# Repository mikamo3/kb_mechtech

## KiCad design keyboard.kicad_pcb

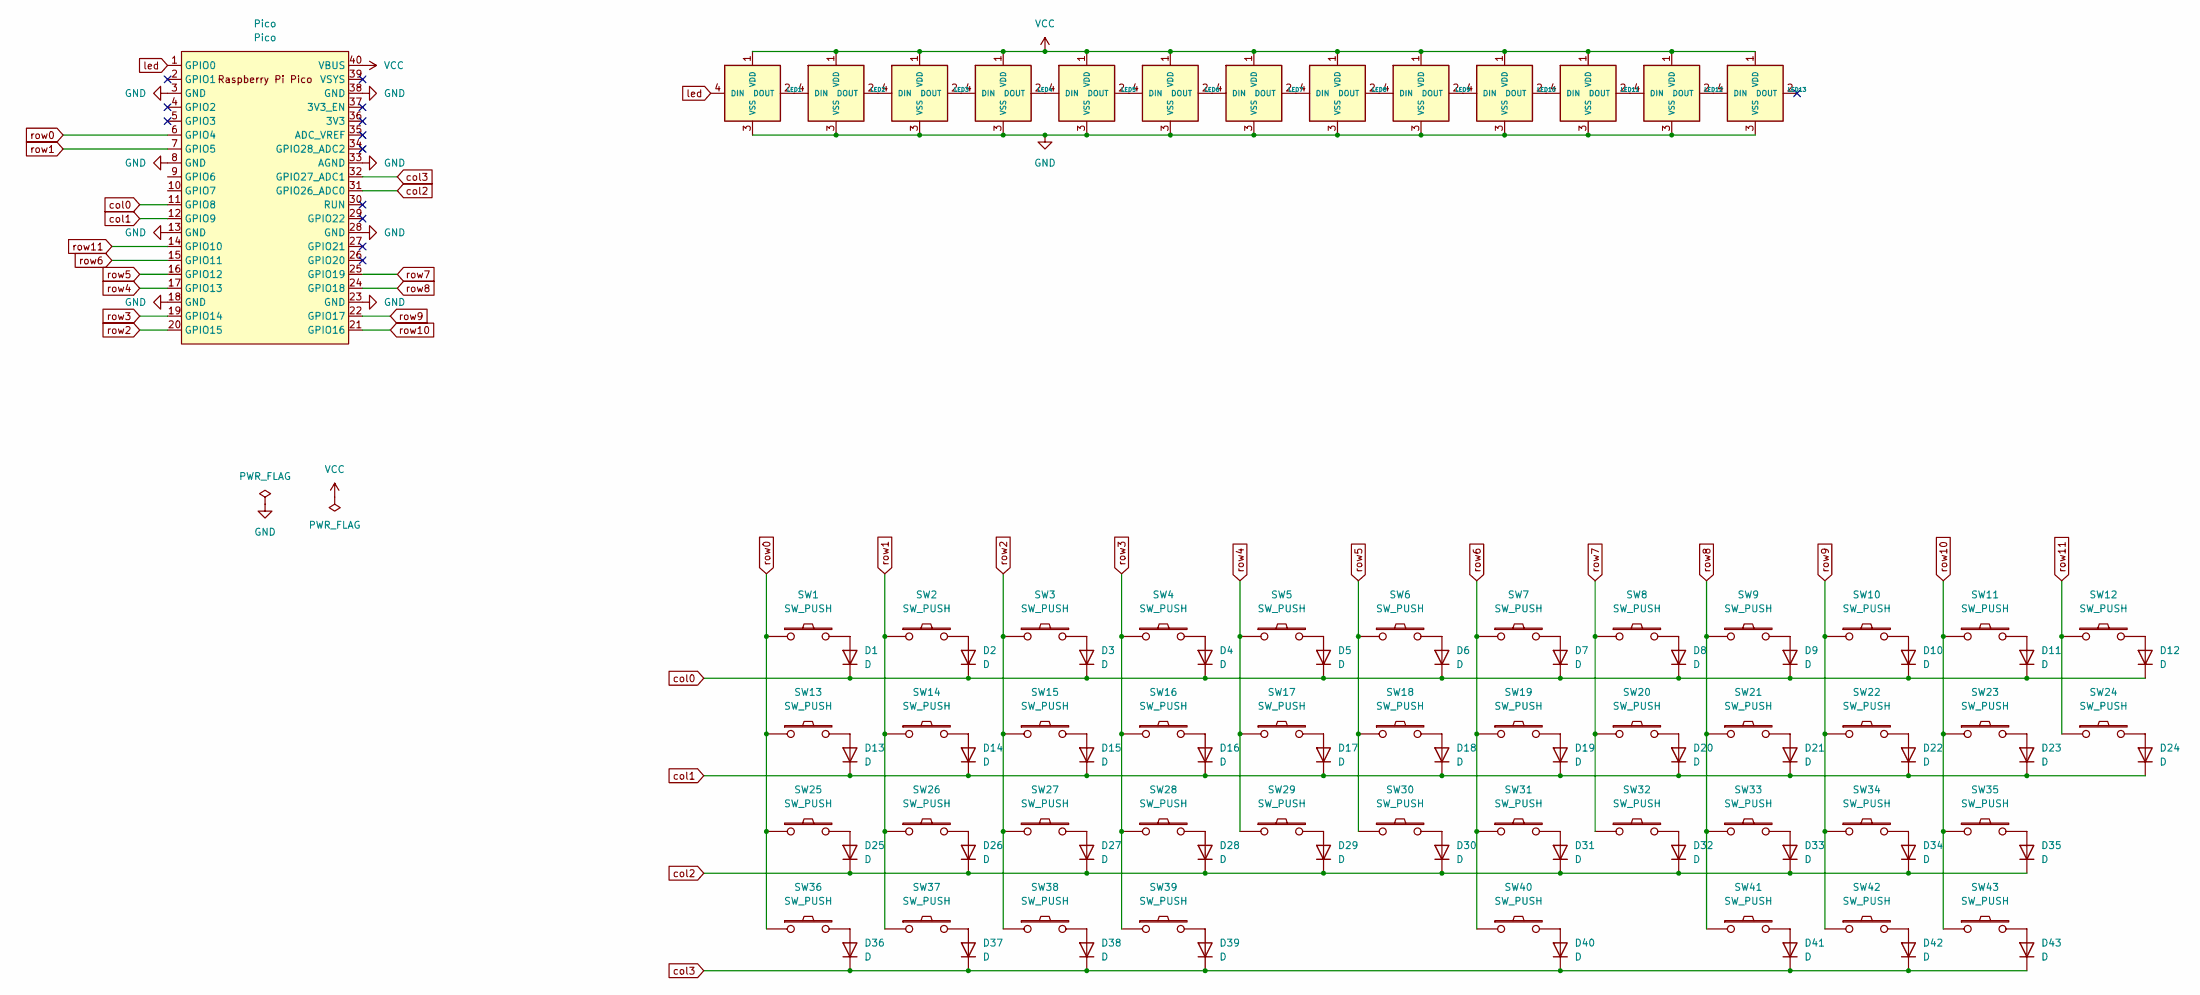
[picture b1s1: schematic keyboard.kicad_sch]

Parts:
D1, D2, D3, D4, D5, D6, D7, D8, D9, D10, D11, D12, D13, D14, D15, D16, D17, D18, D19, D20, D21, D22, D23, D24, D25, D26, D27, D28, D29, D30, D31, D32, D33, D34, D35, D36, D37, D38, D39, D40, D41, D42, D43: D; D_SOD-123
LED1, LED2, LED3, LED4, LED5, LED6, LED7, LED8, LED9, LED10, LED11, LED12, LED13: YS-SK6812MINI-E
Pico: Pico; raspberry_pi_pico
SW1, SW2, SW3, SW4, SW5, SW6, SW7, SW8, SW9, SW10, SW11, SW14, SW15, SW16, SW17, SW18, SW19, SW20, SW21, SW22, SW23, SW26, SW27, SW28, SW29, SW30, SW31, SW32, SW33, SW34: SW_PUSH; CherryMX_Hotswap_1u
SW12: SW_PUSH; CherryMX_Hotswap_2u
SW13, SW25: SW_PUSH; CherryMX_Hotswap_1.75u
SW24, SW35, SW39: SW_PUSH; CherryMX_Hotswap_2.25u
SW36, SW37, SW38, SW41, SW42, SW43: SW_PUSH; CherryMX_Hotswap_1.25u
SW40: SW_PUSH; CherryMX_Hotswap_2.75u

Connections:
GND: LED1.3 (VSS), LED2.3 (VSS), LED3.3 (VSS), LED4.3 (VSS), LED5.3 (VSS), LED6.3 (VSS), LED7.3 (VSS), LED8.3 (VSS), LED9.3 (VSS), LED10.3 (VSS), LED11.3 (VSS), LED12.3 (VSS), LED13.3 (VSS), Pico.3 (GND), Pico.8 (GND), Pico.13 (GND), Pico.18 (GND), Pico.23 (GND), Pico.28 (GND), Pico.33 (AGND), Pico.38 (GND)
unnamed: D1.2 (A), SW1.2
unnamed: D2.2 (A), SW2.2
unnamed: D3.2 (A), SW3.2
unnamed: D4.2 (A), SW4.2
unnamed: D5.2 (A), SW5.2
unnamed: D6.2 (A), SW6.2
unnamed: D7.2 (A), SW7.2
unnamed: D8.2 (A), SW8.2
unnamed: D9.2 (A), SW9.2
unnamed: D10.2 (A), SW10.2
unnamed: D11.2 (A), SW11.2
unnamed: D12.2 (A), SW12.2
unnamed: D13.2 (A), SW13.2
unnamed: D14.2 (A), SW14.2
unnamed: D15.2 (A), SW15.2
unnamed: D16.2 (A), SW16.2
unnamed: D17.2 (A), SW17.2
unnamed: D18.2 (A), SW18.2
unnamed: D19.2 (A), SW19.2
unnamed: D20.2 (A), SW20.2
unnamed: D21.2 (A), SW21.2
unnamed: D22.2 (A), SW22.2
unnamed: D23.2 (A), SW23.2
unnamed: D24.2 (A), SW24.2
unnamed: D25.2 (A), SW25.2
unnamed: D26.2 (A), SW26.2
unnamed: D27.2 (A), SW27.2
unnamed: D28.2 (A), SW28.2
unnamed: D29.2 (A), SW29.2
unnamed: D30.2 (A), SW30.2
unnamed: D31.2 (A), SW31.2
unnamed: D32.2 (A), SW32.2
unnamed: D33.2 (A), SW33.2
unnamed: D34.2 (A), SW34.2
unnamed: D35.2 (A), SW35.2
unnamed: D36.2 (A), SW36.2
unnamed: D37.2 (A), SW37.2
unnamed: D38.2 (A), SW38.2
unnamed: D39.2 (A), SW39.2
unnamed: D40.2 (A), SW40.2
unnamed: D41.2 (A), SW41.2
unnamed: D42.2 (A), SW42.2
unnamed: D43.2 (A), SW43.2
unnamed: LED1.2 (DOUT), LED2.4 (DIN)
unnamed: LED2.2 (DOUT), LED3.4 (DIN)
unnamed: LED3.2 (DOUT), LED4.4 (DIN)
unnamed: LED4.2 (DOUT), LED5.4 (DIN)
unnamed: LED5.2 (DOUT), LED6.4 (DIN)
unnamed: LED6.2 (DOUT), LED7.4 (DIN)
unnamed: LED7.2 (DOUT), LED8.4 (DIN)
unnamed: LED8.2 (DOUT), LED9.4 (DIN)
unnamed: LED10.2 (DOUT), LED11.4 (DIN)
unnamed: LED9.2 (DOUT), LED10.4 (DIN)
unnamed: LED11.2 (DOUT), LED12.4 (DIN)
unnamed: LED12.2 (DOUT), LED13.4 (DIN)
VCC: LED1.1 (VDD), LED2.1 (VDD), LED3.1 (VDD), LED4.1 (VDD), LED5.1 (VDD), LED6.1 (VDD), LED7.1 (VDD), LED8.1 (VDD), LED9.1 (VDD), LED10.1 (VDD), LED11.1 (VDD), LED12.1 (VDD), LED13.1 (VDD), Pico.40 (VBUS)
col0: D1.1 (K), D2.1 (K), D3.1 (K), D4.1 (K), D5.1 (K), D6.1 (K), D7.1 (K), D8.1 (K), D9.1 (K), D10.1 (K), D11.1 (K), D12.1 (K), Pico.11 (GPIO8)
col1: D13.1 (K), D14.1 (K), D15.1 (K), D16.1 (K), D17.1 (K), D18.1 (K), D19.1 (K), D20.1 (K), D21.1 (K), D22.1 (K), D23.1 (K), D24.1 (K), Pico.12 (GPIO9)
col2: D25.1 (K), D26.1 (K), D27.1 (K), D28.1 (K), D29.1 (K), D30.1 (K), D31.1 (K), D32.1 (K), D33.1 (K), D34.1 (K), D35.1 (K), Pico.31 (GPIO26_ADC0)
col3: D36.1 (K), D37.1 (K), D38.1 (K), D39.1 (K), D40.1 (K), D41.1 (K), D42.1 (K), D43.1 (K), Pico.32 (GPIO27_ADC1)
led: LED1.4 (DIN), Pico.1 (GPIO0)
row0: Pico.6 (GPIO4), SW1.1, SW13.1, SW25.1, SW36.1
row1: Pico.7 (GPIO5), SW2.1, SW14.1, SW26.1, SW37.1
row2: Pico.20 (GPIO15), SW3.1, SW15.1, SW27.1, SW38.1
row3: Pico.19 (GPIO14), SW4.1, SW16.1, SW28.1, SW39.1
row4: Pico.17 (GPIO13), SW5.1, SW17.1, SW29.1
row5: Pico.16 (GPIO12), SW6.1, SW18.1, SW30.1
row6: Pico.15 (GPIO11), SW7.1, SW19.1, SW31.1, SW40.1
row7: Pico.25 (GPIO19), SW8.1, SW20.1, SW32.1
row8: Pico.24 (GPIO18), SW9.1, SW21.1, SW33.1, SW41.1
row9: Pico.22 (GPIO17), SW10.1, SW22.1, SW34.1, SW42.1
row10: Pico.21 (GPIO16), SW11.1, SW23.1, SW35.1, SW43.1
row11: Pico.14 (GPIO10), SW12.1, SW24.1

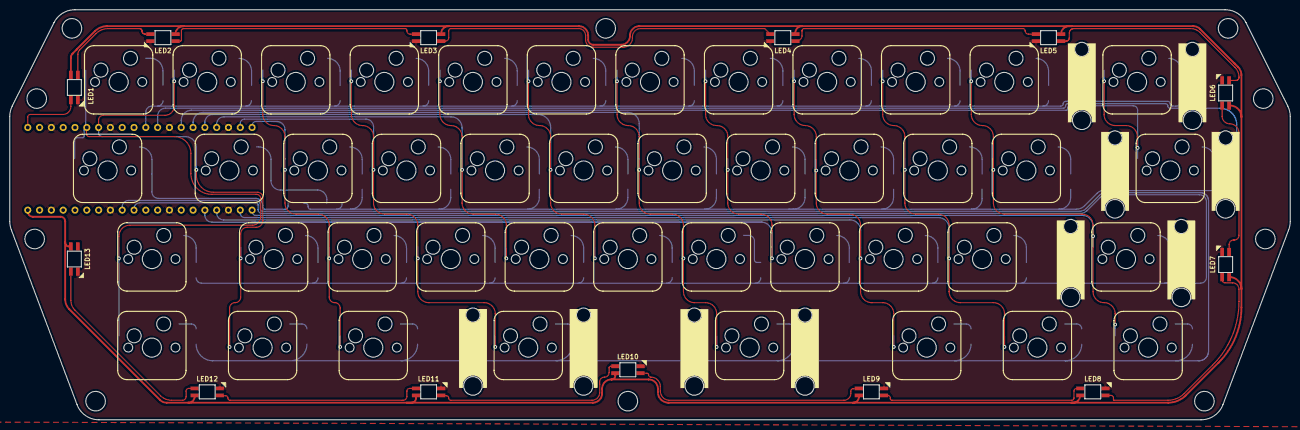
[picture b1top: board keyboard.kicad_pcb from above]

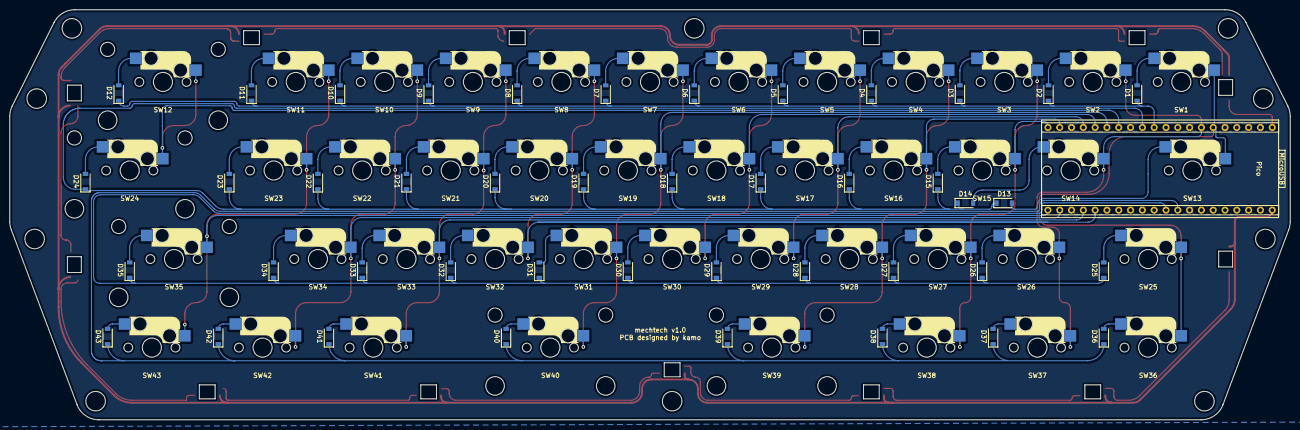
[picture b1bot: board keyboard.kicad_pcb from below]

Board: 2 copper layers, 275.5 x 88.2 mm, 100 parts (44 on the bottom side), 74 nets.

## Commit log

2022-07-02 :sparkles: (all) firstcommit
2022-07-03 :wrench: (gitignore) add
2022-07-03 :sparkles: (sch) create
2022-07-06 :sparkles: (pcb) in preparation
2022-07-16 :construction:
2022-08-07 :sparkles: (all) before pcb order
2022-08-07 :ambulance: (fix before order)
2022-08-11 :bug: (middleplate) fix
2022-08-21 :sparkles: (layout) add legend
2022-08-21 :sparkles: (prk_firmware) add keymap
2022-08-21 :bug: (layout) fix
2022-08-25 :bug: (keymap) fix keycode
2022-08-25 :bug: (keymap) fix
2022-08-25 :bug: (keymap) add KC_BSLS
2023-06-17 :sparkles: (all) Add
